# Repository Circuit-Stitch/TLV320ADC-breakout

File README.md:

# ADC breakout

A four-channel, line-level ADC board built around the TI TLV320ADC6140. It is a KiCad 10 project.

The board sends TDM audio out and is controlled over I2C. It connects to a Raspberry Pi Pico 2 by jumper wires. It was built as the real ADC for the RP2350 capture tests in portacorder, a portable 32-bit float recorder.

The parts and reference designators match `docs/bom.md`.

The board is also a [PCBWay shared project](https://www.pcbway.com/project/shareproject/TLV320_ADC_breakout_33a37ab8.html). You can order it there with assembly.

| Front | Back |
|-------|------|
|  |  |

## Files

- `adc-breakout.kicad_pro` is the project. Open it in KiCad.
- `adc-breakout.kicad_sch` is the schematic.
- `adc-breakout.kicad_pcb` is the 4-layer PCB.
- `adc-breakout.pdf` is a PDF export of the schematic.
- `pfr.kicad_sym` is the project symbol library. It holds the TLV320ADC6140 symbol. KiCad has no stock symbol for this part.
- `sym-lib-table` adds `pfr.kicad_sym` to the project.
- `gerbers/version 1/` holds the rev 1 fabrication files. `gerbers/version 1.zip` is the same set, zipped for upload.
- `jlcpcb/` holds the JLCPCB assembly BOM and placement (CPL) files for rev 1.
- `pcbway/` holds the assembly BOM, with manufacturer part numbers, and the centroid file for the PCBWay shared project.
- `docs/bom.md` is the bill of materials, with prices, stock, and part notes.
- `docs/oscillator-selection.md` compares the 24.576 MHz oscillators considered for Y1 and for portacorder Rev A.
- `renders/` holds the front and back board renders and a STEP model of the assembled board.
- `datasheets/tlv320adc6140.pdf` is the ADC datasheet.
- `datasheets/ASTX-H11.pdf` is the Y1 oscillator datasheet.
- The other files in `datasheets/` are the oscillator datasheets cited in `docs/oscillator-selection.md`.

All other symbols and footprints come from the stock KiCad 10 libraries.

## Headers

| Header | Pins |
|--------|------|
| J1, power and control | 1 +5V, 2 +3V3, 3 GND, 4 SDA, 5 SCL, 6 SHDNZ, 7 GND, 8 GND |
| J2, audio bus | 1 FSYNC, 2 GND, 3 BCLK, 4 GND, 5 SDOUT, 6 GND |
| J3–J6, line inputs CH1–CH4 | 1 CHx_IN_J+ (tip), 2 CHx_IN_J- (ring), 3 GND (sleeve) |

Each input is balanced line level, wired straight to the ADC through its coupling caps. The ADC clips at about 2 Vrms differential, about +8 dBu. There is no phantom power and no phantom protection.

The ADC side of each coupling cap is `CHx_IN+` or `CHx_IN-`. Each `+`/`-` pair routes as a differential pair in the PCB editor.

## Changes from the BOM

C10 and C11 ground to GND. Route each ground terminal straight to U1 pin 4 (AVSS), with no via, as the datasheet layout guidelines require.

JP1 and JP2 are 3-pad solder jumpers. The BOM lists 2-pad jumpers. Pads 1–2 are bridged to GND by default, which gives I2C address 0x4C. To change the address, cut 1–2 and bridge 2–3 to IOVDD. A cut 2-pad jumper would leave the address pin floating.

## Footprint checks

- Y1 uses the stock Abracon ASE footprint for 3.2 × 2.5 mm oscillators. Check its pads against the ASTX-H11 datasheet, `datasheets/ASTX-H11.pdf`.
- U1 uses the TI RTW footprint with thermal vias, `Texas_RTW_WQFN-24-1EP_4x4mm_P0.5mm_EP2.7x2.7mm_ThermalVias`. The thermal pad is pin 25.

## License

The design is licensed under the CERN Open Hardware Licence Version 2 – Weakly Reciprocal (CERN-OHL-W-2.0). See `LICENSE`.

The PDFs in `datasheets/` belong to their manufacturers. The license does not cover them.

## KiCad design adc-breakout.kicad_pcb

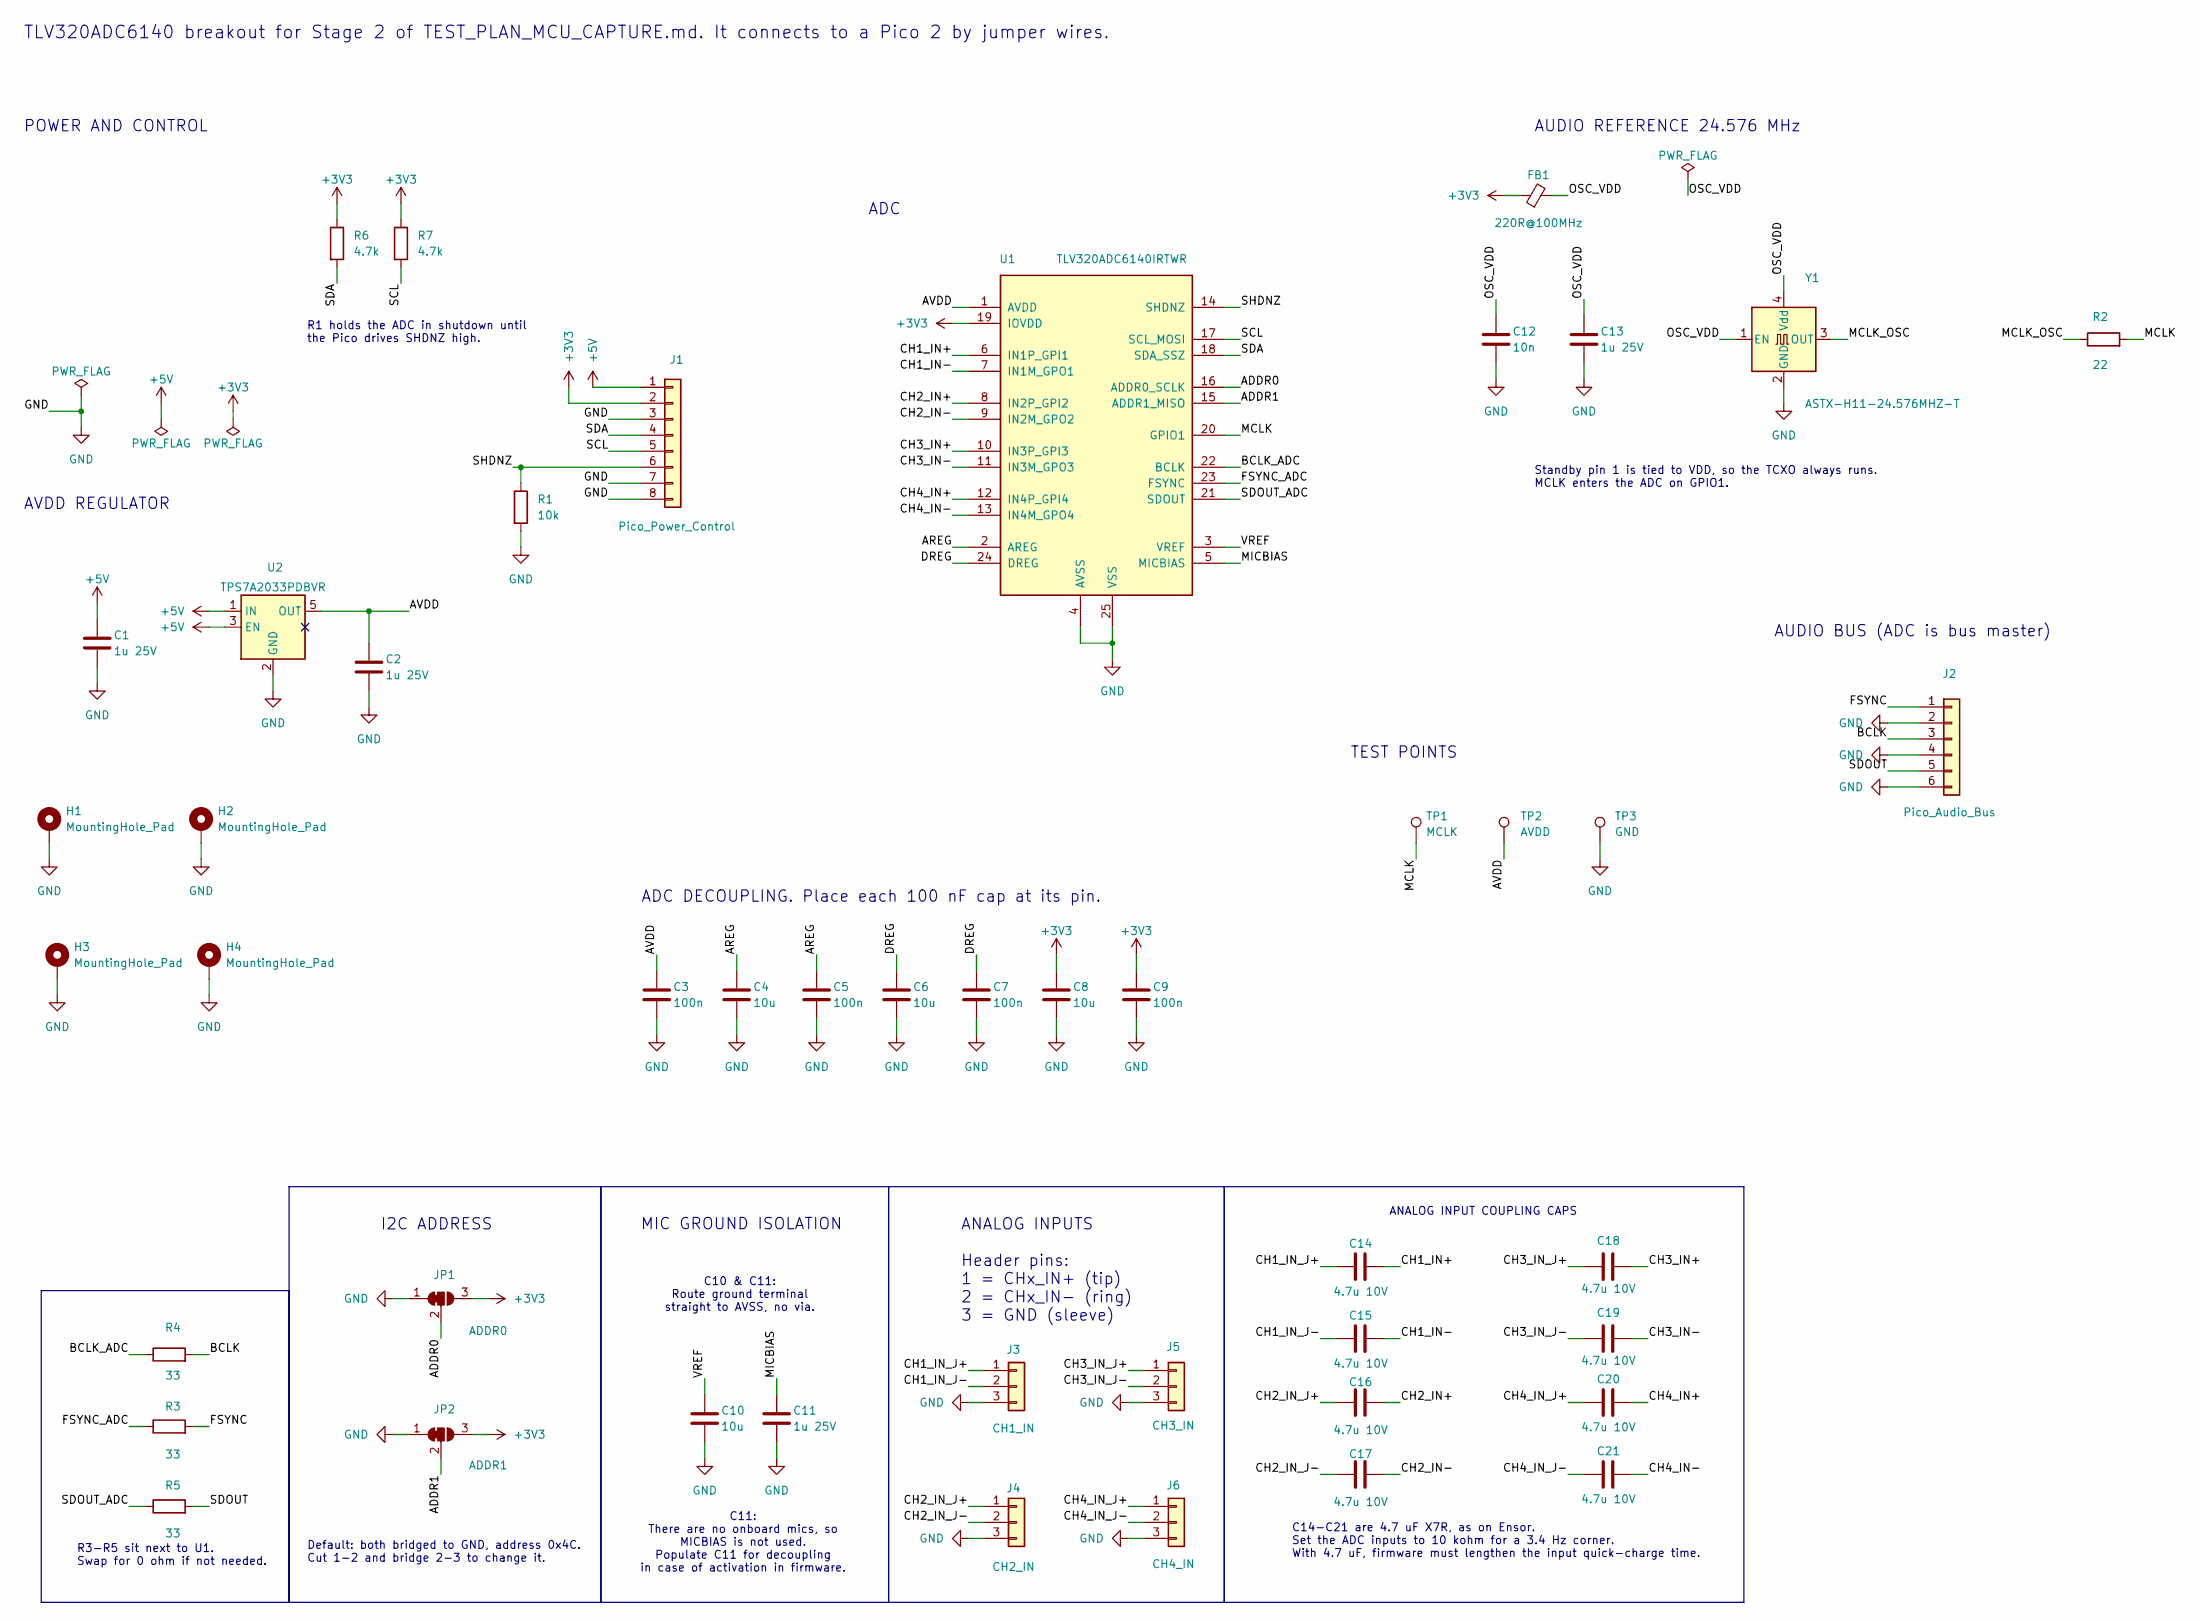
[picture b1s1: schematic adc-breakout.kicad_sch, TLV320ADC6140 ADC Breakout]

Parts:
C1, C2, C11, C13: 1u 25V; C_0603_1608Metric; MPN Kyocera AVX 06033C105KAT4A
C3, C5, C7, C9: 100n; C_0402_1005Metric; MPN Murata GRM155R71C104KA88D
C4, C6, C8, C10: 10u; C_0603_1608Metric; MPN Murata GRT188R61A106KE13D
C12: 10n; C_0402_1005Metric; MPN Murata GRM155R71C103KA01D
C14, C15, C16, C17, C18, C19, C20, C21: 4.7u 10V; C_0805_2012Metric; MPN Kyocera AVX 0805ZC475KAT2A
FB1: 220R@100MHz; L_0603_1608Metric; MPN Murata BLM18PG221SN1D
H1, H2, H3, H4: MountingHole_Pad; MountingHole_2.7mm_M2.5_Pad_Via
J1: Pico_Power_Control; PinHeader_1x08_P2.54mm_Vertical
J2: Pico_Audio_Bus; PinHeader_1x06_P2.54mm_Vertical
J3: CH1_IN; PinHeader_1x03_P2.54mm_Vertical
J4: CH2_IN; PinHeader_1x03_P2.54mm_Vertical
J5: CH3_IN; PinHeader_1x03_P2.54mm_Vertical
J6: CH4_IN; PinHeader_1x03_P2.54mm_Vertical
JP1: ADDR0; SolderJumper-3_P1.3mm_Bridged12_RoundedPad1.0x1.5mm
JP2: ADDR1; SolderJumper-3_P1.3mm_Bridged12_RoundedPad1.0x1.5mm
R1: 10k; R_0402_1005Metric; MPN Yageo RC0402FR-0710KL
R2: 22; R_0402_1005Metric; MPN Yageo RC0402FR-0722RL
R3, R4, R5: 33; R_0402_1005Metric; MPN Yageo RC0402FR-0733RL
R6, R7: 4.7k; R_0402_1005Metric; MPN Yageo RC0402FR-074K7L
TP1: MCLK; TestPoint_Pad_D1.5mm
TP2: AVDD; TestPoint_Pad_D1.5mm
TP3: GND; TestPoint_Pad_D1.5mm
U1: TLV320ADC6140IRTWR; Texas_RTW_WQFN-24-1EP_4x4mm_P0.5mm_EP2.7x2.7mm_ThermalVias
U2: TPS7A2033PDBVR; SOT-23-5
Y1: ASTX-H11-24.576MHZ-T; Oscillator_SMD_Abracon_ASE-4Pin_3.2x2.5mm; MPN Abracon ASTX-H11-24.576MHZ-T

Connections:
+3V3: C8.1, C9.1, FB1.1, J1.2, JP1.3 (B), JP2.3 (B), R6.1, R7.1, U1.19 (IOVDD)
+5V: C1.1, J1.1, U2.1 (IN), U2.3 (EN)
/ADDR0: JP1.2 (C), U1.16 (ADDR0_SCLK)
/ADDR1: JP2.2 (C), U1.15 (ADDR1_MISO)
/AREG: C4.1, C5.1, U1.2 (AREG)
/AVDD: C2.1, C3.1, TP2.1 (1_1), U1.1 (AVDD), U2.5 (OUT)
/BCLK: J2.3, R4.2
/BCLK_ADC: R4.1, U1.22 (BCLK)
/CH1_IN+: C14.2, U1.6 (IN1P_GPI1)
/CH1_IN-: C15.2, U1.7 (IN1M_GPO1)
/CH1_IN_J+: C14.1, J3.1
/CH1_IN_J-: C15.1, J3.2
/CH2_IN+: C16.2, U1.8 (IN2P_GPI2)
/CH2_IN-: C17.2, U1.9 (IN2M_GPO2)
/CH2_IN_J+: C16.1, J4.1
/CH2_IN_J-: C17.1, J4.2
/CH3_IN+: C18.2, U1.10 (IN3P_GPI3)
/CH3_IN-: C19.2, U1.11 (IN3M_GPO3)
/CH3_IN_J+: C18.1, J5.1
/CH3_IN_J-: C19.1, J5.2
/CH4_IN+: C20.2, U1.12 (IN4P_GPI4)
/CH4_IN-: C21.2, U1.13 (IN4M_GPO4)
/CH4_IN_J+: C20.1, J6.1
/CH4_IN_J-: C21.1, J6.2
/DREG: C6.1, C7.1, U1.24 (DREG)
/FSYNC: J2.1, R3.2
/FSYNC_ADC: R3.1, U1.23 (FSYNC)
/MCLK: R2.2, TP1.1 (1_1), U1.20 (GPIO1)
/MCLK_OSC: R2.1, Y1.3 (OUT)
/MICBIAS: C11.1, U1.5 (MICBIAS)
/OSC_VDD: C12.1, C13.1, FB1.2, Y1.1 (EN), Y1.4 (Vdd)
/SCL: J1.5, R7.2, U1.17 (SCL_MOSI)
/SDA: J1.4, R6.2, U1.18 (SDA_SSZ)
/SDOUT: J2.5, R5.2
/SDOUT_ADC: R5.1, U1.21 (SDOUT)
/SHDNZ: J1.6, R1.1, U1.14 (SHDNZ)
/VREF: C10.1, U1.3 (VREF)
GND: C1.2, C2.2, C3.2, C4.2, C5.2, C6.2, C7.2, C8.2, C9.2, C10.2, C11.2, C12.2, C13.2, H1.1 (1_1), H2.1 (1_1), H3.1 (1_1), H4.1 (1_1), J1.3, J1.7, J1.8, J2.2, J2.4, J2.6, J3.3, J4.3, J5.3, J6.3, JP1.1 (A), JP2.1 (A), R1.2, TP3.1 (1_1), U1.4 (AVSS), U1.25 (VSS), U2.2 (GND), Y1.2 (GND)

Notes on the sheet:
Standby pin 1 is tied to VDD, so the TCXO always runs. MCLK enters the ADC on GPIO1.
C11: There are no onboard mics, so MICBIAS is not used. Populate C11 for decoupling in case of activation in firmware.
TLV320ADC6140 breakout for Stage 2 of TEST_PLAN_MCU_CAPTURE.md. It connects to a Pico 2 by jumper wires.
MIC GROUND ISOLATION
AUDIO BUS (ADC is bus master)
TEST POINTS
R1 holds the ADC in shutdown until the Pico drives SHDNZ high.
ANALOG INPUT COUPLING CAPS
Default: both bridged to GND, address 0x4C. Cut 1-2 and bridge 2-3 to change it.
R3-R5 sit next to U1. Swap for 0 ohm if not needed.
ADC DECOUPLING. Place each 100 nF cap at its pin.
C10 & C11: Route ground terminal straight to AVSS, no via.
C14-C21 are 4.7 uF X7R, as on Ensor. Set the ADC inputs to 10 kohm for a 3.4 Hz corner. With 4.7 uF, firmware must lengthen the input quick-charge time.
I2C ADDRESS
POWER AND CONTROL
AUDIO REFERENCE 24.576 MHz
ADC
ANALOG INPUTS Header pins: 1 = CHx_IN+ (tip) 2 = CHx_IN- (ring) 3 = GND (sleeve)
AVDD REGULATOR

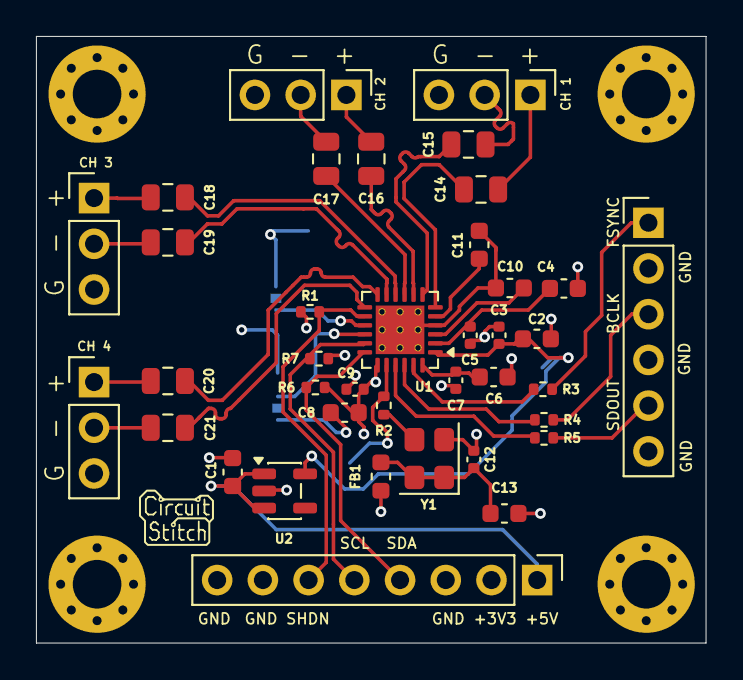
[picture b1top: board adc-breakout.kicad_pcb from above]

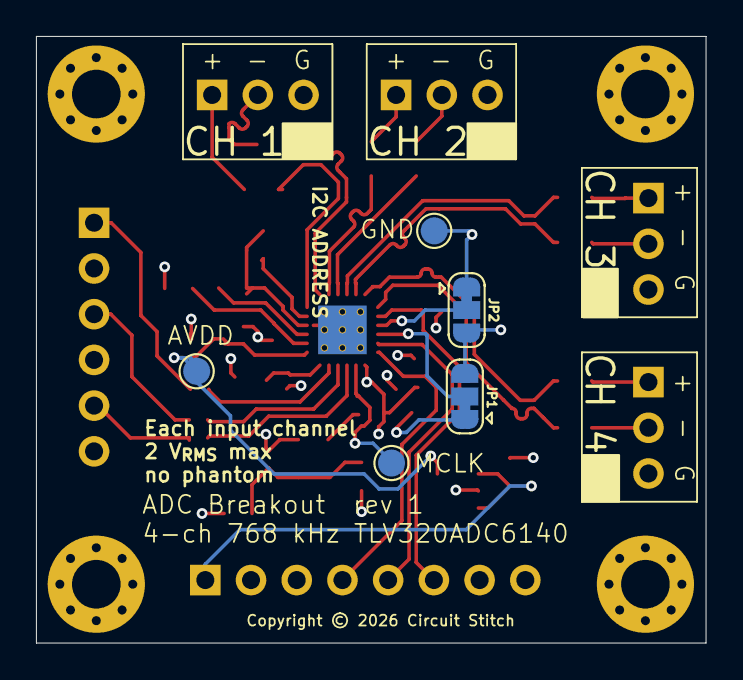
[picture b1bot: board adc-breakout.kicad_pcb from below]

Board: 4 copper layers, 37.2 x 33.7 mm, 47 parts (5 on the bottom side), 38 nets.

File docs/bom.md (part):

# Bill of Materials

Quantities are for one board. Stock and prices were checked on 2026-10-12. A dash means not yet priced.

Status: **Chosen** = part number fixed. **Candidate** = likely, not confirmed. **TBD** = not picked.

Digi-Key prices marked `Digi-Key*` come from Digi-Key's USD mirror site, which shows no stock and may be stale. Stock for those parts comes from digikey.ca. Every Digi-Key listing carries a possible US tariff. Mouser could not be reached. LCSC prices are live USD.

The support parts follow the Ensor-384 board, dated 2024-11-13.

## Parts

Power comes from the Pico 2 header. 5 V feeds the AVDD regulator. The Pico 3.3 V rail feeds IOVDD and the oscillator, as on Ensor.

| Ref       | Item                    | Part                                              | Qty | Status    | Price at 1 | Price at 100 | Source    | Notes                                                                                                                                       |
|-----------|-------------------------|---------------------------------------------------|-----|-----------|------------|--------------|-----------|---------------------------------------------------------------------------------------------------------------------------------------------|
| U1        | Audio ADC               | TI TLV320ADC6140IRTWR, WQFN-24 4×4 mm             | 1   | Chosen    | $7.53      | $4.89        | Digi-Key  | 744 in stock at Digi-Key, 12-week lead time. Owner confirmed on Digi-Key US. LCSC C1852020 has 1 at $11.15. TI store out of stock. I2C 0x4C with ADDR0 and ADDR1 grounded  |
| U2        | AVDD regulator          | TI TPS7A2033PDBVR, 3.3 V, SOT-23-5                | 1   | Candidate | $0.21      | $0.16 at 50  | LCSC      | C2862740, 178,020 in stock. Low noise, 300 mA. Digi-Key has 0 until 2026-11-23. Ensor uses TPS73533. Backup: LP5907MFX-3.3/NOPB             |
| Y1        | Audio reference         | Abracon ASTX-H11-24.576MHZ-T, 3.2×2.5 mm          | 1   | Chosen    | $4.37      | $3.30        | Digi-Key* | ±2.5 ppm TCXO. 556 in stock, 16-week lead time. JLCPCB C1987701. Standby pin tied to 3.3 V. Same part as Ensor. See [`oscillator-selection.md`](oscillator-selection.md)                                 |
| FB1       | Oscillator supply bead  | Murata BLM18PG221SN1D, 0603                       | 1   | Candidate | $0.10      | $0.04        | Digi-Key* | 220 Ω at 100 MHz. Isolates the oscillator from the Pico 3.3 V rail. 235,085 in stock                                                        |
| R1        | SHDNZ pull-down         | Yageo RC0402FR-0710KL, 10 kΩ                      | 1   | Chosen    | —          | $0.01        | Digi-Key  | Holds the ADC in shutdown until the Pico drives SHDNZ high. Meets the power-up sequence. Same as Ensor                                      |
| R2        | MCLK series             | Yageo RC0402FR-0722RL, 22 Ω                       | 1   | Candidate | —          | —            | —         | Oscillator to GPIO1. Same value as Ensor                                                                                                    |
| R3–R5     | Audio bus series        | Yageo RC0402FR-0733RL, 33 Ω                       | 3   | Candidate | —          | $0.004       | LCSC      | R3 FSYNC, R4 BCLK, R5 SDOUT. Ensor has none. Added for the jumper wires to the Pico. Swap for 0 Ω if not needed                                      |
| R6, R7    | I2C pull-ups            | Yageo RC0402FR-074K7L, 4.7 kΩ                     | 2   | Candidate | —          | $0.01        | Digi-Key  | Digi-Key has 0 until 2026-11-09. Any 4.7 kΩ 1% 0402 fits                                                                                    |
| JP1, JP2  | Address jumpers         | Solder jumper, default to GND                     | 2   | Chosen    | —          | —            | —         | ADDR0 and ADDR1. Cut to change the I2C address                                                                                              |
| C1        | LDO input               | Kyocera AVX 06033C105KAT4A, 1 µF 25 V X7R 0603    | 1   | Chosen    | $0.40      | $0.152       | Digi-Key  | 12,980 in stock                                                                                                                             |
| C2        | AVDD                    | Kyocera AVX 06033C105KAT4A, 1 µF 25 V X7R 0603    | 1   | Chosen    | $0.40      | $0.152       | Digi-Key  | Also serves as the LDO output cap                                                                                                           |
| C3, C5, C7, C9 | Pin decoupling     | Murata GRM155R71C104KA88D, 100 nF 16 V X7R 0402   | 4   | Chosen    | $0.12      | $0.017       | Mouser    | AVDD, AREG, DREG, IOVDD. Price from the warm-dimmer BOM. LCSC C71629 is $0.005 at 100                                                       |
| C4, C6, C8, C10 | Bulk                | Murata GRT188R61A106KE13D, 10 µF 10 V X5R 0603    | 4   | Chosen    | $0.34      | $0.128       | Mouser    | AREG, DREG, IOVDD, VREF. Replaces GRM188R61A106KE69D, limited availability, as in the sister projects. LCSC C77044 still lists that part at $0.028. Ensor uses 10 µF on VREF; the datasheet minimum is 1 µF |
| C11       | MICBIAS                 | Kyocera AVX 06033C105KAT4A, 1 µF 25 V X7R 0603    | 1   | Chosen    | $0.40      | $0.152       | Digi-Key  | Fitted even with MICBIAS unused. Ground terminal straight to AVSS, no via                                                                   |
| C12       | Oscillator, HF          | Murata GRM155R71C103KA01D, 10 nF 16 V X7R 0402    | 1   | Chosen    | $0.11      | $0.014       | Mouser    | Price from the warm-dimmer BOM. Same value as Ensor                                                                                         |
| C13       | Oscillator, bulk        | Kyocera AVX 06033C105KAT4A, 1 µF 25 V X7R 0603    | 1   | Candidate | $0.40      | $0.152       | Digi-Key  | After FB1                                                                                                                                   |
| C14–C21   | Input coupling          | Kyocera AVX 0805ZC475KAT2A, 4.7 µF 10 V X7R 0805  | 8   | Candidate | —          | —            | —         | One per INxP and INxM. Same as Ensor. TI recommends low voltage coefficient for best distortion; see note below                            |
| J1        | Power and control       | 1×8 pin header, 2.54 mm                           | 1   | TBD       | —          | —            | —         | 5 V, 3.3 V, GND, SDA, SCL, SHDNZ, GND, GND                                                                                                  |
| J2        | Audio bus               | 1×6 pin header, 2.54 mm                           | 1   | TBD       | —          | —            | —         | FSYNC, GND, BCLK, GND, SDOUT, GND. Matches the U1 pin order. A ground next to each signal                                                                             |
| J3–J6     | Analog inputs           | 1×3 pin header, 2.54 mm                           | 4   | TBD       | —          | —            | —         | INxP, INxM, GND per channel. Pigtail to TRS for the MOTU                                                                                    |
| TP1–TP3   | Test points             | MCLK, AVDD, GND                                   | 3   | TBD       | —          | —            | —         | Scope access                                                                                                                                |
| —         | PCB                     | 4-layer, 1 oz                                     | 1   | Candidate | —          | —            | —         | Solid ground plane under U1. Thermal pad vias to ground                                                                                     |
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

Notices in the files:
adc-breakout.kicad_pcb:
Copyright © 2026 Circuit Stitch
